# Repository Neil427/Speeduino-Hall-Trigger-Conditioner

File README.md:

# KiwiEFI-HallSensor-Conditioner
Speeduino Hall sensor conditioner board with buffering:   
This KiwiEfi project is a dual Hall effect sensor conditioner board designed with the form factor to plug into a Speeduino ECU
The conditioner has many features to help diagnostics, protect the mcu, and configuration for different engines.
- Dual Channel
- Output buffering to drive the mcu and protect the mcu from overvoltage sources
- Crank and Cam trigger LED indication
- Selectable signal filtering
- Selectable signal polarity invert function
- Selectable inversion of the indicator LEDs to suit the polarity of the input signal

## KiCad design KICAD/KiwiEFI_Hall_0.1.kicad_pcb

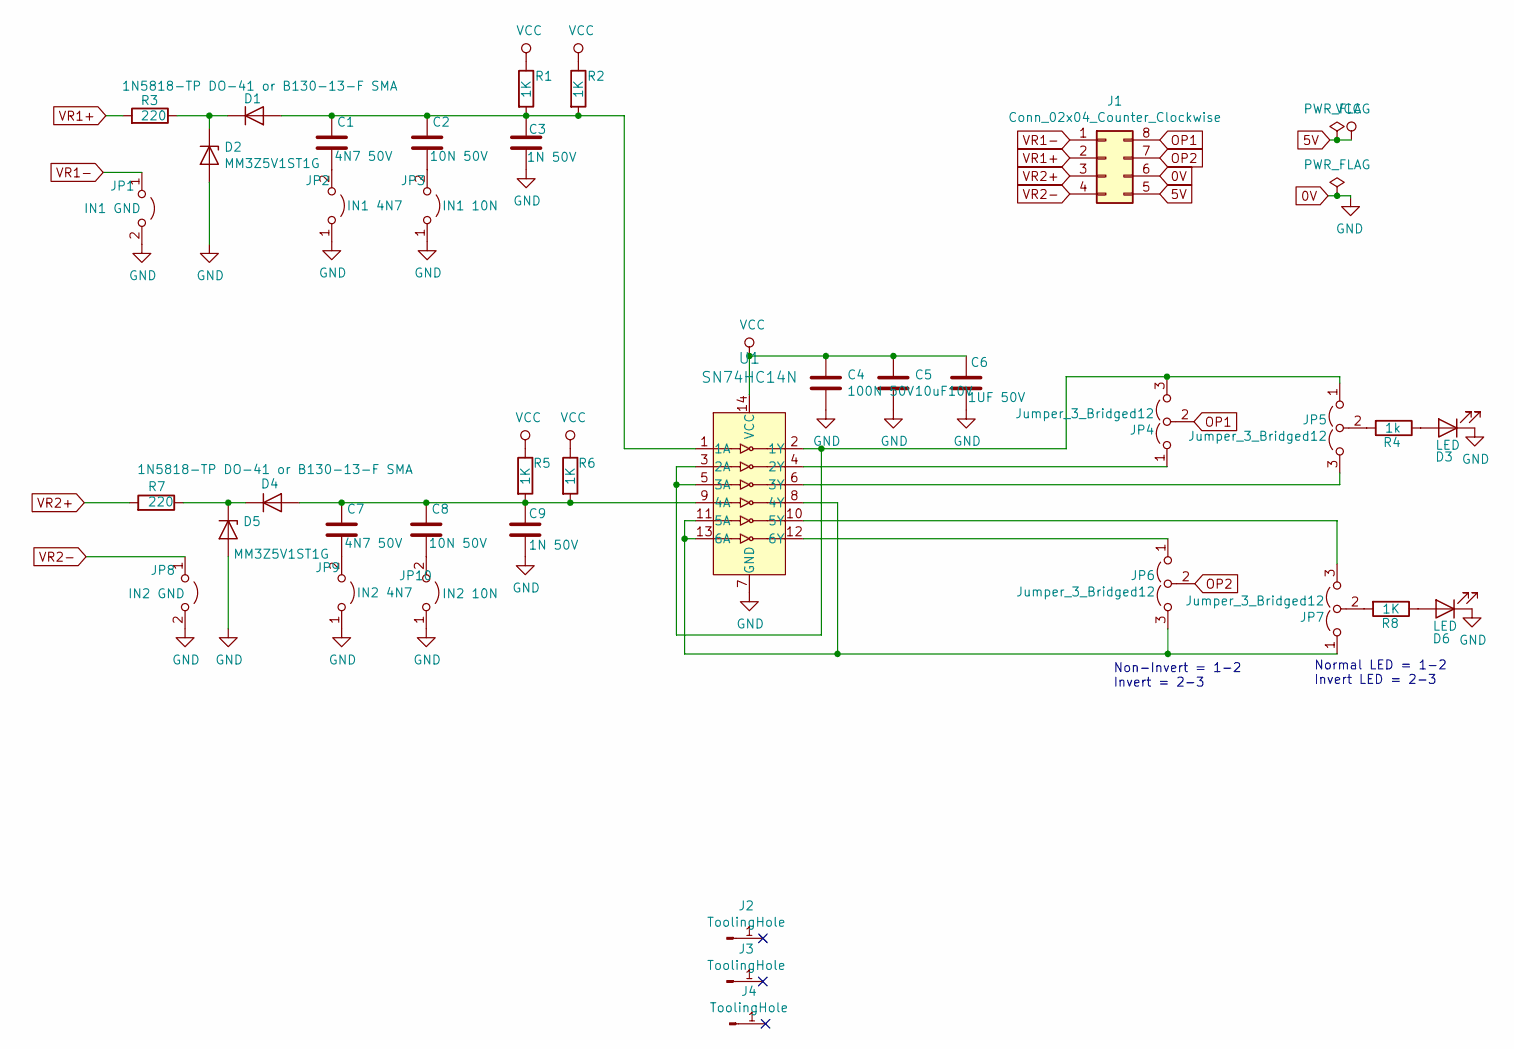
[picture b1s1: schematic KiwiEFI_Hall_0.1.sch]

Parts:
C1, C7: 4N7 50V; C_0805_2012Metric_Pad1.15x1.40mm_HandSolder
C2, C8: 10N 50V; C_0805_2012Metric_Pad1.15x1.40mm_HandSolder
C3, C9: 1N 50V; C_0805_2012Metric_Pad1.15x1.40mm_HandSolder
C4: 100N 50V; C_0805_2012Metric_Pad1.15x1.40mm_HandSolder
C5: 10uF10V; C_0805_2012Metric_Pad1.15x1.40mm_HandSolder
C6: 1UF 50V; C_0805_2012Metric_Pad1.15x1.40mm_HandSolder
D1, D4: 1N5818-TP DO-41 or B130-13-F SMA; D_SMA_Handsoldering
D2, D5: MM3Z5V1ST1G; D_SOD-323_HandSoldering
D3, D6: LED; LED_0805_2012Metric_Pad1.15x1.40mm_HandSolder
J1: Conn_02x04_Counter_Clockwise; DIP-8_W7.62mm_LongPads
J2, J3, J4: ToolingHole
JP1: IN1 GND; SolderJumper-2_P1.3mm_Open_RoundedPad1.0x1.5mm
JP2: IN1 4N7; SolderJumper-2_P1.3mm_Open_RoundedPad1.0x1.5mm
JP3: IN1 10N; SolderJumper-2_P1.3mm_Open_RoundedPad1.0x1.5mm
JP4, JP5, JP6, JP7: Jumper_3_Bridged12; SolderJumper-3_P1.3mm_Open_RoundedPad1.0x1.5mm_NumberLabels
JP8: IN2 GND; SolderJumper-2_P1.3mm_Open_RoundedPad1.0x1.5mm
JP9: IN2 4N7; SolderJumper-2_P1.3mm_Open_RoundedPad1.0x1.5mm
JP10: IN2 10N; SolderJumper-2_P1.3mm_Open_RoundedPad1.0x1.5mm
R1, R2, R5, R6, R8: 1K; R_0805_2012Metric_Pad1.15x1.40mm_HandSolder
R3, R7: 220; R_0805_2012Metric_Pad1.15x1.40mm_HandSolder
R4: 1k; R_0805_2012Metric_Pad1.15x1.40mm_HandSolder
U1: SN74HC14N; SOIC-14_3.9x8.7mm_P1.27mm; MPN SN74HC14N; Digi-Key_PN 296-1577-5-ND

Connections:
0V: C3.2, C4.2, C5.2, C6.2, C9.2, D2.2 (A), D3.1 (K), D5.2 (A), D6.1 (K), J1.6, JP1.2 (B), JP2.1 (A), JP3.1 (A), JP8.2 (B), JP9.1 (A), JP10.1 (A), U1.7 (GND)
5V: C4.1, C5.1, C6.1, J1.5, R1.1, R2.1, R5.1, R6.1, U1.14 (VCC)
unnamed: C1.1, C2.1, C3.1, D1.2 (A), R1.2, R2.2, U1.1 (1A)
unnamed: C1.2, JP2.2 (B)
unnamed: C2.2, JP3.2 (B)
unnamed: C7.1, C8.1, C9.1, D4.2 (A), R5.2, R6.2, U1.9 (4A)
unnamed: C7.2, JP9.2 (B)
unnamed: C8.2, JP10.2 (B)
unnamed: D1.1 (K), D2.1 (K), R3.1
unnamed: D3.2 (A), R4.1
unnamed: D4.1 (K), D5.1 (K), R7.1
unnamed: D6.2 (A), R8.1
unnamed: JP4.1 (A), U1.4 (2Y)
unnamed: JP4.3 (B), JP5.1 (A), U1.2 (1Y), U1.3 (2A), U1.5 (3A)
unnamed: JP5.2 (C), R4.2
unnamed: JP5.3 (B), U1.6 (3Y)
unnamed: JP6.1 (A), U1.12 (6Y)
unnamed: JP6.3 (B), JP7.1 (A), U1.8 (4Y), U1.11 (5A), U1.13 (6A)
unnamed: JP7.2 (C), R8.2
unnamed: JP7.3 (B), U1.10 (5Y)
OP1: J1.8, JP4.2 (C)
OP2: J1.7, JP6.2 (C)
VR1+: J1.2, R3.2
VR1-: J1.1, JP1.1 (A)
VR2+: J1.3, R7.2
VR2-: J1.4, JP8.1 (A)

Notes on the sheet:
Non-Invert = 1-2 Invert = 2-3
Normal LED = 1-2 Invert LED = 2-3

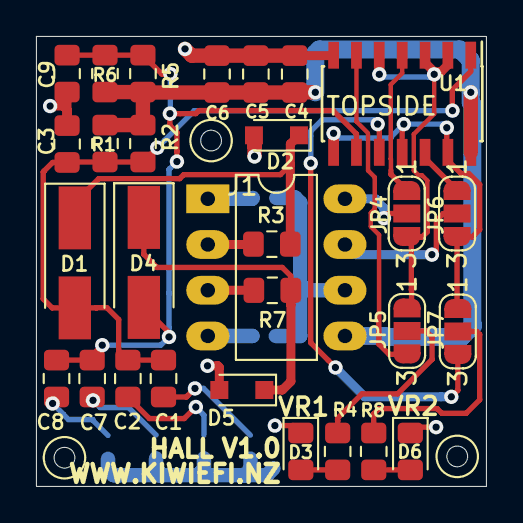
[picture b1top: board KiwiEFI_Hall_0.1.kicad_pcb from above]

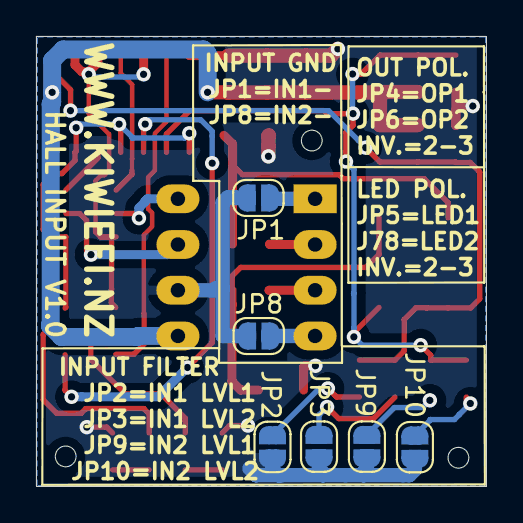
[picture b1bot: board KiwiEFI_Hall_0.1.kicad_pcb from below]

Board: 2 copper layers, 25.0 x 25.0 mm, 38 parts (6 on the bottom side), 26 nets.

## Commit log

2021-04-22 Create LICENSE
2021-04-22 Added KIcad files
2021-04-22 Update Schematic
2021-04-23 Pictures Added
2021-04-23 Minor edit
2021-04-23 Doccumenting optional components
2021-04-23 Added configuration document
